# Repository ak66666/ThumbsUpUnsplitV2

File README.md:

# ThumbsUpUnsplitV2
Multilevel 44 Key Ergonomic Keyboard.
V2 puts the fourth row one level up.

The board uses Kailh Choc hot-swap switches.

//TODO Pictures to be replaced.

/20220219_191523.jpg)
/20220219_191651.jpg)
/20220219_152609.jpg)
/20220219_184854.jpg)
/20220219_184909.jpg)
/20220219_191540.jpg)
/20220219_191637.jpg)

# Firmware
                                                               
The board uses Planck rev4 software with one pin replaced - it is needed for Cirque trackpad.
To make it work - modify \qmk_firmware\keyboards\planck\config.h, replace the pin definition with this one:

#define MATRIX_COL_PINS { D7, B4, D6, D4, F7, F6, F5, F4, C7, B0, F0, F1 }

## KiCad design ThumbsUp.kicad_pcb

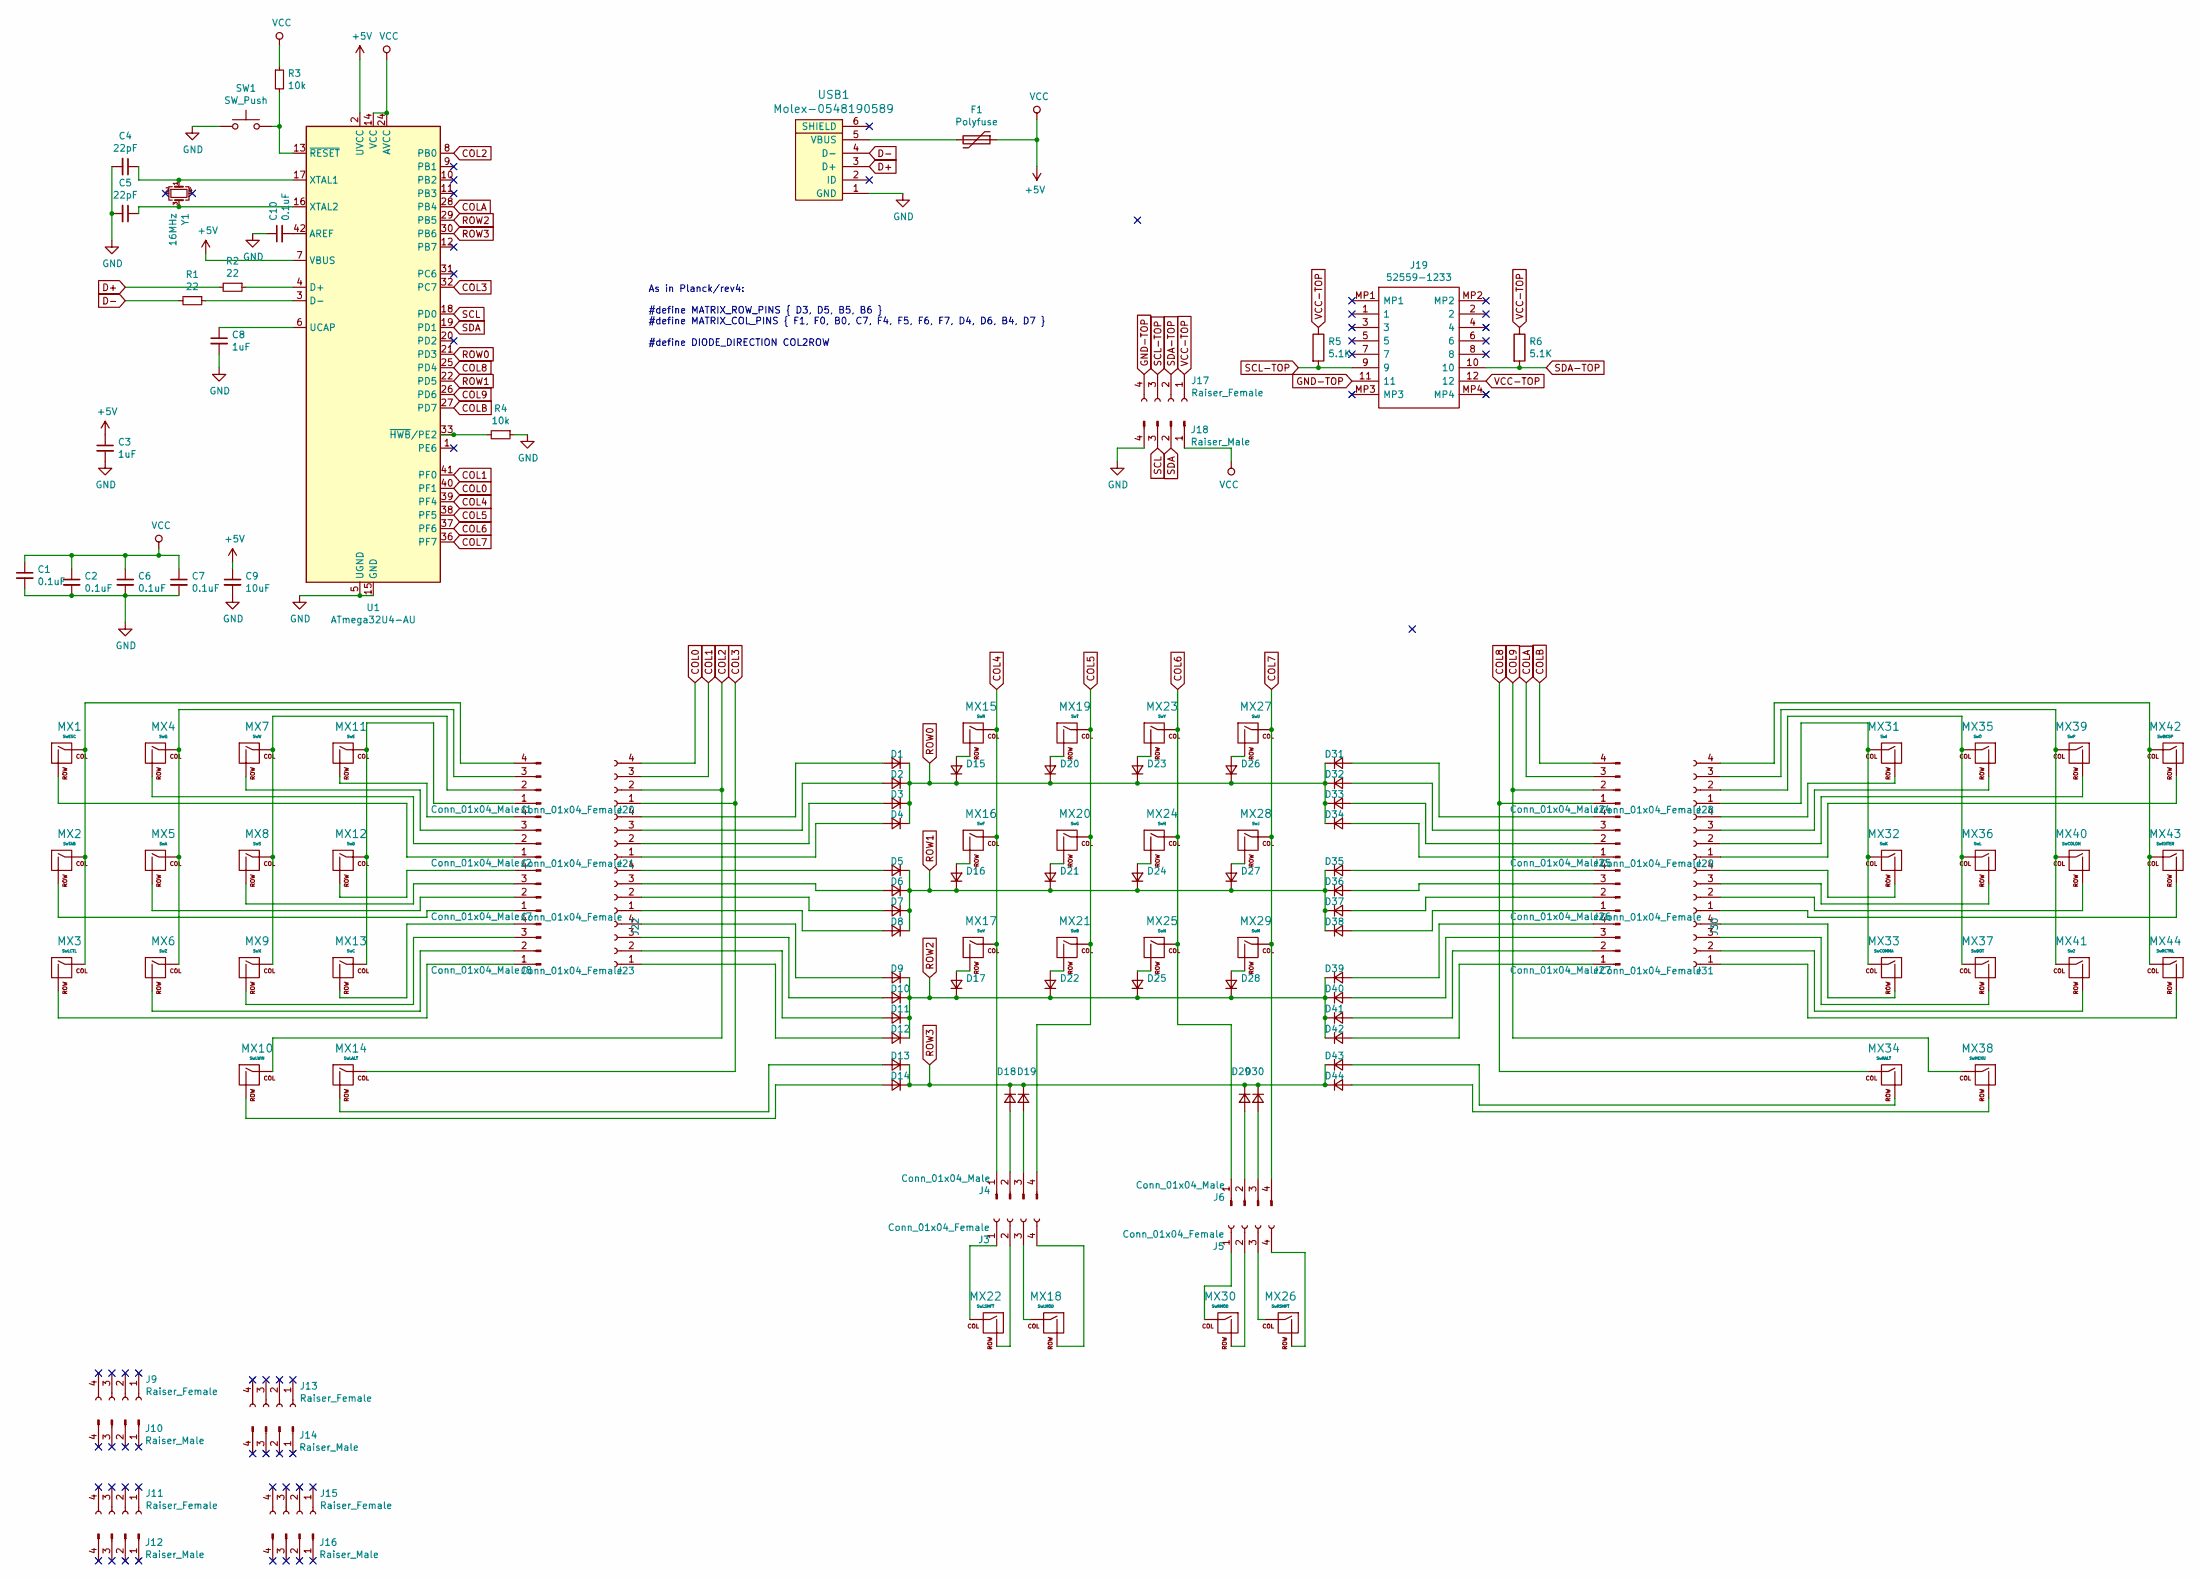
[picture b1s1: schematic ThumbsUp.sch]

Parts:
C1, C2, C6, C7, C10: 0.1uF; C_0805_2012Metric
C3, C8: 1uF; C_0805_2012Metric
C4, C5: 22pF; C_0805_2012Metric
C9: 10uF; C_0805_2012Metric
D1, D2, D3, D4, D5, D6, D7, D8, D9, D10, D11, D12, D13, D14, D15, D16, D17, D18, D19, D20, D21, D22, D23, D24, D25, D26, D27, D28, D29, D30, D31, D32, D33, D34, D35, D36, D37, D38, D39, D40, D41, D42, D43, D44: D_Small; D_SOD-123
F1: Polyfuse; Fuse_1206_3216Metric
J1, J2, J4, J6, J7, J8, J24, J25, J26, J27: Conn_01x04_Male; PinHeader_1x04_P2.54mm_Vertical
J3, J5, J20, J21, J22, J23, J28, J29, J30, J31: Conn_01x04_Female; PinSocket_1x04_P2.54mm_Vertical
J9, J11, J13, J15, J17: Raiser_Female; PinSocket_1x04_P2.54mm_Vertical
J10, J12, J14, J16, J18: Raiser_Male; PinHeader_1x04_P2.54mm_Vertical
J19: 52559-1233; 525591233; Mouser Part Number 538-52559-1233
MX1: SwESC; Kailh_socket_PG1350_optional
MX2: SwTAB; Kailh_socket_PG1350_optional
MX3: SwLCTL; Kailh_socket_PG1350_optional
MX4: SwQ; Kailh_socket_PG1350_optional
MX5: SwA; Kailh_socket_PG1350_optional
MX6: SwZ; Kailh_socket_PG1350_optional
MX7: SwW; Kailh_socket_PG1350_optional
MX8: SwS; Kailh_socket_PG1350_optional
MX9: SwX; Kailh_socket_PG1350_optional
MX10: SwLWIN; Kailh_socket_PG1350_optional
MX11: SwE; Kailh_socket_PG1350_optional
MX12: SwD; Kailh_socket_PG1350_optional
MX13: SwC; Kailh_socket_PG1350_optional
MX14: SwLALT; Kailh_socket_PG1350_optional
MX15: SwR; Kailh_socket_PG1350_optional
MX16: SwF; Kailh_socket_PG1350_optional
MX17: SwV; Kailh_socket_PG1350_optional
MX18: SwLMOD; Kailh_socket_PG1350_optional
MX19: SwT; Kailh_socket_PG1350_optional
MX20: SwG; Kailh_socket_PG1350_optional
MX21: SwB; Kailh_socket_PG1350_optional
MX22: SwLSHFT; Kailh_socket_PG1350_optional
MX23: SwY; Kailh_socket_PG1350_optional
MX24: SwH; Kailh_socket_PG1350_optional
MX25: SwN; Kailh_socket_PG1350_optional
MX26: SwRSHFT; Kailh_socket_PG1350_optional
MX27: SwU; Kailh_socket_PG1350_optional
MX28: SwJ; Kailh_socket_PG1350_optional
MX29: SwM; Kailh_socket_PG1350_optional
MX30: SwRMOD; Kailh_socket_PG1350_optional
MX31: SwI; Kailh_socket_PG1350_optional
MX32: SwK; Kailh_socket_PG1350_optional
MX33: SwCOMMA; Kailh_socket_PG1350_optional
MX34: SwRALT; Kailh_socket_PG1350_optional
MX35: SwO; Kailh_socket_PG1350_optional
MX36: SwL; Kailh_socket_PG1350_optional
MX37: SwDOT; Kailh_socket_PG1350_optional
MX38: SwMENU; Kailh_socket_PG1350_optional
MX39: SwP; Kailh_socket_PG1350_optional
MX40: SwCOLON; Kailh_socket_PG1350_optional
MX41: Sw?; Kailh_socket_PG1350_optional
MX42: SwBKSP; Kailh_socket_PG1350_optional
MX43: SwENTER; Kailh_socket_PG1350_optional
MX44: SwRCTRL; Kailh_socket_PG1350_optional
R1, R2: 22; R_0805_2012Metric
R3, R4: 10k; R_0805_2012Metric
R5, R6: 5.1K; R_0805_2012Metric
SW1: SW_Push; SKQG-1155865
U1: ATmega32U4-AU; TQFP-44_10x10mm_P0.8mm
USB1: Molex-0548190589
Y1: 16MHz; Crystal_SMD_3225-4Pin_3.2x2.5mm_HandSoldering

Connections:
+5V: C1.1, C2.1, C3.1, C6.1, C7.1, C9.1, F1.1, J18.1, R3.1, U1.2 (UVCC), U1.7 (VBUS), U1.14 (VCC), U1.24 (AVCC), U1.34 (VCC), U1.44 (AVCC)
COL0: J20.4, U1.40 (PF1)
COL1: J20.3, U1.41 (PF0)
COL2: J20.2, MX10.1 (COL), U1.8 (PB0)
COL3: J20.1, MX14.1 (COL), U1.32 (PC7)
COL4: J4.1, MX15.1 (COL), MX16.1 (COL), MX17.1 (COL), U1.39 (PF4)
COL5: J4.4, MX19.1 (COL), MX20.1 (COL), MX21.1 (COL), U1.38 (PF5)
COL6: J6.1, MX23.1 (COL), MX24.1 (COL), MX25.1 (COL), U1.37 (PF6)
COL7: J6.4, MX27.1 (COL), MX28.1 (COL), MX29.1 (COL), U1.36 (PF7)
COL8: J24.1, MX34.1 (COL), U1.25 (PD4)
COL9: J24.2, MX38.1 (COL), U1.26 (PD6)
COLA: J24.3, U1.28 (PB4)
COLB: J24.4, U1.27 (PD7)
D+: R2.2, USB1.3 (D+)
D-: R1.2, USB1.4 (D-)
GND: C1.2, C2.2, C3.2, C4.2, C5.2, C6.2, C7.2, C8.2, C9.2, C10.1, J18.4, R4.1, SW1.1, U1.5 (UGND), U1.15 (GND), U1.23 (GND), U1.35 (GND), U1.43 (GND), USB1.1 (GND)
GND-TOP: J17.4, J19.11
unnamed: C4.1, U1.17 (XTAL1), Y1.1
unnamed: C5.1, U1.16 (XTAL2), Y1.3
unnamed: C8.1, U1.6 (UCAP)
unnamed: C10.2, U1.42 (AREF)
unnamed: D1.2 (A), J21.4
unnamed: D2.2 (A), J21.3
unnamed: D3.2 (A), J21.2
unnamed: D4.2 (A), J21.1
unnamed: D5.2 (A), J22.4
unnamed: D6.2 (A), J22.3
unnamed: D7.2 (A), J22.2
unnamed: D8.2 (A), J22.1
unnamed: D9.2 (A), J23.4
unnamed: D10.2 (A), J23.3
unnamed: D11.2 (A), J23.2
unnamed: D12.2 (A), J23.1
unnamed: D13.2 (A), MX14.2 (ROW)
unnamed: D14.2 (A), MX10.2 (ROW)
unnamed: D15.2 (A), MX15.2 (ROW)
unnamed: D16.2 (A), MX16.2 (ROW)
unnamed: D17.2 (A), MX17.2 (ROW)
unnamed: D18.2 (A), J4.2
unnamed: D19.2 (A), J4.3
unnamed: D20.2 (A), MX19.2 (ROW)
unnamed: D21.2 (A), MX20.2 (ROW)
unnamed: D22.2 (A), MX21.2 (ROW)
unnamed: D23.2 (A), MX23.2 (ROW)
unnamed: D24.2 (A), MX24.2 (ROW)
unnamed: D25.2 (A), MX25.2 (ROW)
unnamed: D26.2 (A), MX27.2 (ROW)
unnamed: D27.2 (A), MX28.2 (ROW)
unnamed: D28.2 (A), MX29.2 (ROW)
unnamed: D29.2 (A), J6.2
unnamed: D30.2 (A), J6.3
unnamed: D31.2 (A), J25.4
unnamed: D32.2 (A), J25.3
unnamed: D33.2 (A), J25.2
unnamed: D34.2 (A), J25.1
unnamed: D35.2 (A), J26.4
unnamed: D36.2 (A), J26.3
unnamed: D37.2 (A), J26.2
unnamed: D38.2 (A), J26.1
unnamed: D39.2 (A), J27.4
unnamed: D40.2 (A), J27.3
unnamed: D41.2 (A), J27.2
unnamed: D42.2 (A), J27.1
unnamed: D43.2 (A), MX34.2 (ROW)
unnamed: D44.2 (A), MX38.2 (ROW)
unnamed: F1.2, USB1.5 (VBUS)
unnamed: J1.1, MX11.1 (COL), MX12.1 (COL), MX13.1 (COL)
unnamed: J1.2, MX7.1 (COL), MX8.1 (COL), MX9.1 (COL)
unnamed: J1.3, MX4.1 (COL), MX5.1 (COL), MX6.1 (COL)
unnamed: J1.4, MX1.1 (COL), MX2.1 (COL), MX3.1 (COL)
unnamed: J2.1, MX1.2 (ROW)
unnamed: J2.2, MX4.2 (ROW)
unnamed: J2.3, MX7.2 (ROW)
unnamed: J2.4, MX11.2 (ROW)
unnamed: J3.1, MX22.1 (COL)
unnamed: J3.2, MX22.2 (ROW)
unnamed: J3.3, MX18.1 (COL)
unnamed: J3.4, MX18.2 (ROW)
unnamed: J5.1, MX30.1 (COL)
unnamed: J5.2, MX30.2 (ROW)
unnamed: J5.3, MX26.1 (COL)
unnamed: J5.4, MX26.2 (ROW)
unnamed: J7.1, MX2.2 (ROW)
unnamed: J7.2, MX5.2 (ROW)
unnamed: J7.3, MX8.2 (ROW)
unnamed: J7.4, MX12.2 (ROW)
unnamed: J8.1, MX3.2 (ROW)
unnamed: J8.2, MX6.2 (ROW)
unnamed: J8.3, MX9.2 (ROW)
unnamed: J8.4, MX13.2 (ROW)
unnamed: J28.1, MX31.1 (COL), MX32.1 (COL), MX33.1 (COL)
unnamed: J28.2, MX35.1 (COL), MX36.1 (COL), MX37.1 (COL)
unnamed: J28.3, MX39.1 (COL), MX40.1 (COL), MX41.1 (COL)
unnamed: J28.4, MX42.1 (COL), MX43.1 (COL), MX44.1 (COL)
unnamed: J29.1, MX42.2 (ROW)
unnamed: J29.2, MX39.2 (ROW)
unnamed: J29.3, MX35.2 (ROW)
unnamed: J29.4, MX31.2 (ROW)
unnamed: J30.1, MX43.2 (ROW)
unnamed: J30.2, MX40.2 (ROW)
unnamed: J30.3, MX36.2 (ROW)
unnamed: J30.4, MX32.2 (ROW)
unnamed: J31.1, MX44.2 (ROW)
unnamed: J31.2, MX41.2 (ROW)
unnamed: J31.3, MX37.2 (ROW)
unnamed: J31.4, MX33.2 (ROW)
unnamed: R1.1, U1.3 (D-)
unnamed: R2.1, U1.4 (D+)
unnamed: R3.2, SW1.2, U1.13 (~RESET)
unnamed: R4.2, U1.33 (~HWB~/PE2)
ROW0: D1.1 (K), D2.1 (K), D3.1 (K), D4.1 (K), D15.1 (K), D20.1 (K), D23.1 (K), D26.1 (K), D31.1 (K), D32.1 (K), D33.1 (K), D34.1 (K), U1.21 (PD3)
ROW1: D5.1 (K), D6.1 (K), D7.1 (K), D8.1 (K), D16.1 (K), D21.1 (K), D24.1 (K), D27.1 (K), D35.1 (K), D36.1 (K), D37.1 (K), D38.1 (K), U1.22 (PD5)
ROW2: D9.1 (K), D10.1 (K), D11.1 (K), D12.1 (K), D17.1 (K), D22.1 (K), D25.1 (K), D28.1 (K), D39.1 (K), D40.1 (K), D41.1 (K), D42.1 (K), U1.29 (PB5)
ROW3: D13.1 (K), D14.1 (K), D18.1 (K), D19.1 (K), D29.1 (K), D30.1 (K), D43.1 (K), D44.1 (K), U1.30 (PB6)
SCL: J18.3, U1.18 (PD0)
SCL-TOP: J17.3, J19.9, R5.2
SDA: J18.2, U1.19 (PD1)
SDA-TOP: J17.2, J19.10, R6.2
VCC-TOP: J17.1, J19.12, R5.1, R6.1

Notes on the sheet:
As in Planck/rev4: #define MATRIX_ROW_PINS { D3, D5, B5, B6 } #define MATRIX_COL_PINS { F1, F0, B0, C7, F4, F5, F6, F7, D4, D6, B4, D7 } #define DIODE_DIRECTION COL2ROW

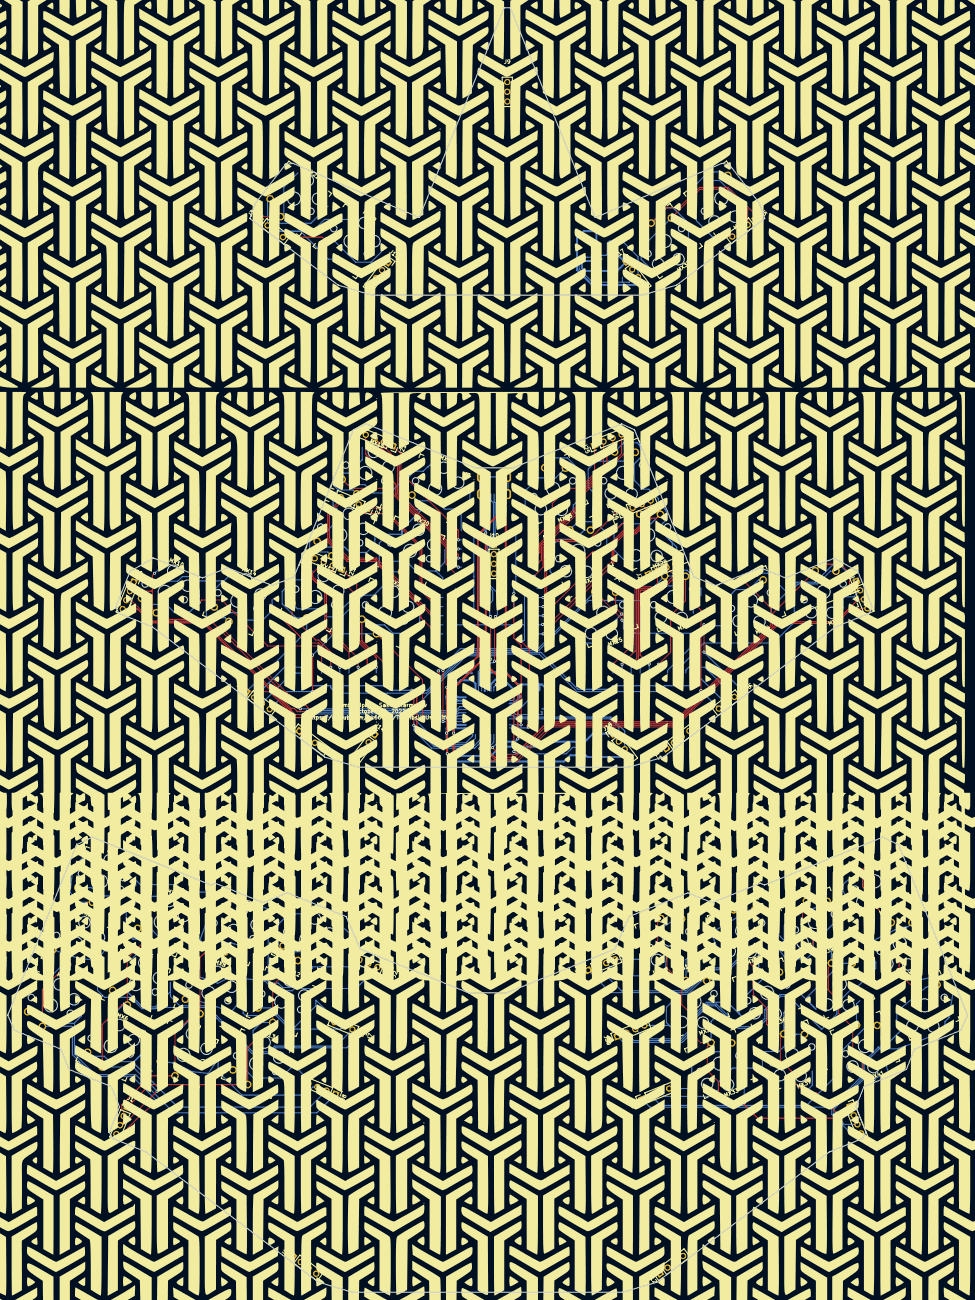
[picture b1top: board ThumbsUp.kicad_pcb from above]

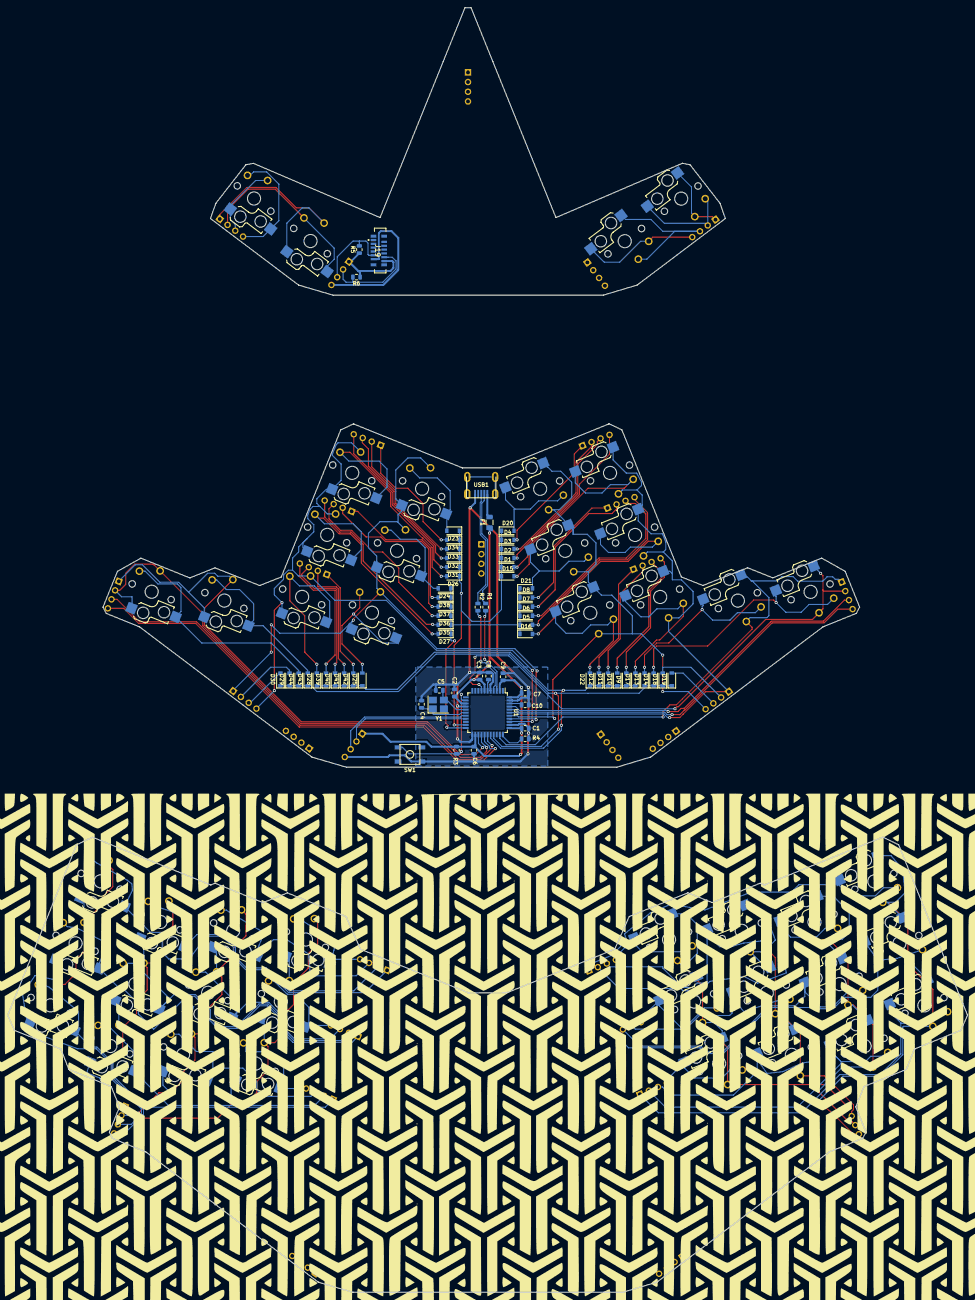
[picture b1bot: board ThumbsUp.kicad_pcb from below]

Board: 2 copper layers, 251.1 x 336.1 mm, 140 parts (66 on the bottom side), 119 nets.

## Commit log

2022-10-11 Initial version
2022-10-16 Added the trackpad socket
2022-10-21 Started the layout
2022-10-22 Working on the layout
2022-10-23 Split the boards
2022-10-23 End of the day resuls
2022-10-30 Laid some tracks
2022-10-30 Tracks are almost finished
2022-10-30 Removed the exta footprints
2022-11-03 Somewhat completed the development
2022-11-10 Moved the tracks from under MCU
2022-11-11 Redrew the middle board
2022-11-23 Swapped space and shift keys
2022-11-24 Somewhat complete
2022-12-05 Moved the touchpad connector
2022-12-12 Regenerated Gerber for the top layer
2022-12-18 Added pullup resistors for trackpad, re-produced the gerbers
